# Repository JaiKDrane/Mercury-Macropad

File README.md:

# Mercury

## License

This repository uses a split licensing model:

* **Hardware & CAD ('/hardware', '/cad'):** Licensed under the **CERN Open Hardware Licence Version 2 - Strongly Reciprocal** ([CERN-OHL-S v2](hardware/LICENSE-HARDWARE.txt))
* **Firmware ('/firmware'):** Licensed under the **GNU General Public License v3.0** ([GPLv3](firmware/LICENSE)) due to QMK dependencies.

*Blender rendering of what the finished product might look like.*

## Purpose
The Mercury macropad is a 16+1 key macro pad aimed at being useful for a variety of purposes, featuring an OLED screen, a rotary encoder, and 16 customizable macro-keys. The design is centered around a nice!nano and nice!view, as well as Hotswap Kalih MX sockets.

You can either use the ([.STL](hardware/MercuryCase.stl)) or the ([View-Only Onshape Link](https://cad.onshape.com/documents/36be8d2820c932561b6e754c/w/a382f2a567d932feba75c19c/e/c855985b69218710006a8b27?renderMode=0&uiState=6aff60ae90390abc054af3d9)) to view the design.

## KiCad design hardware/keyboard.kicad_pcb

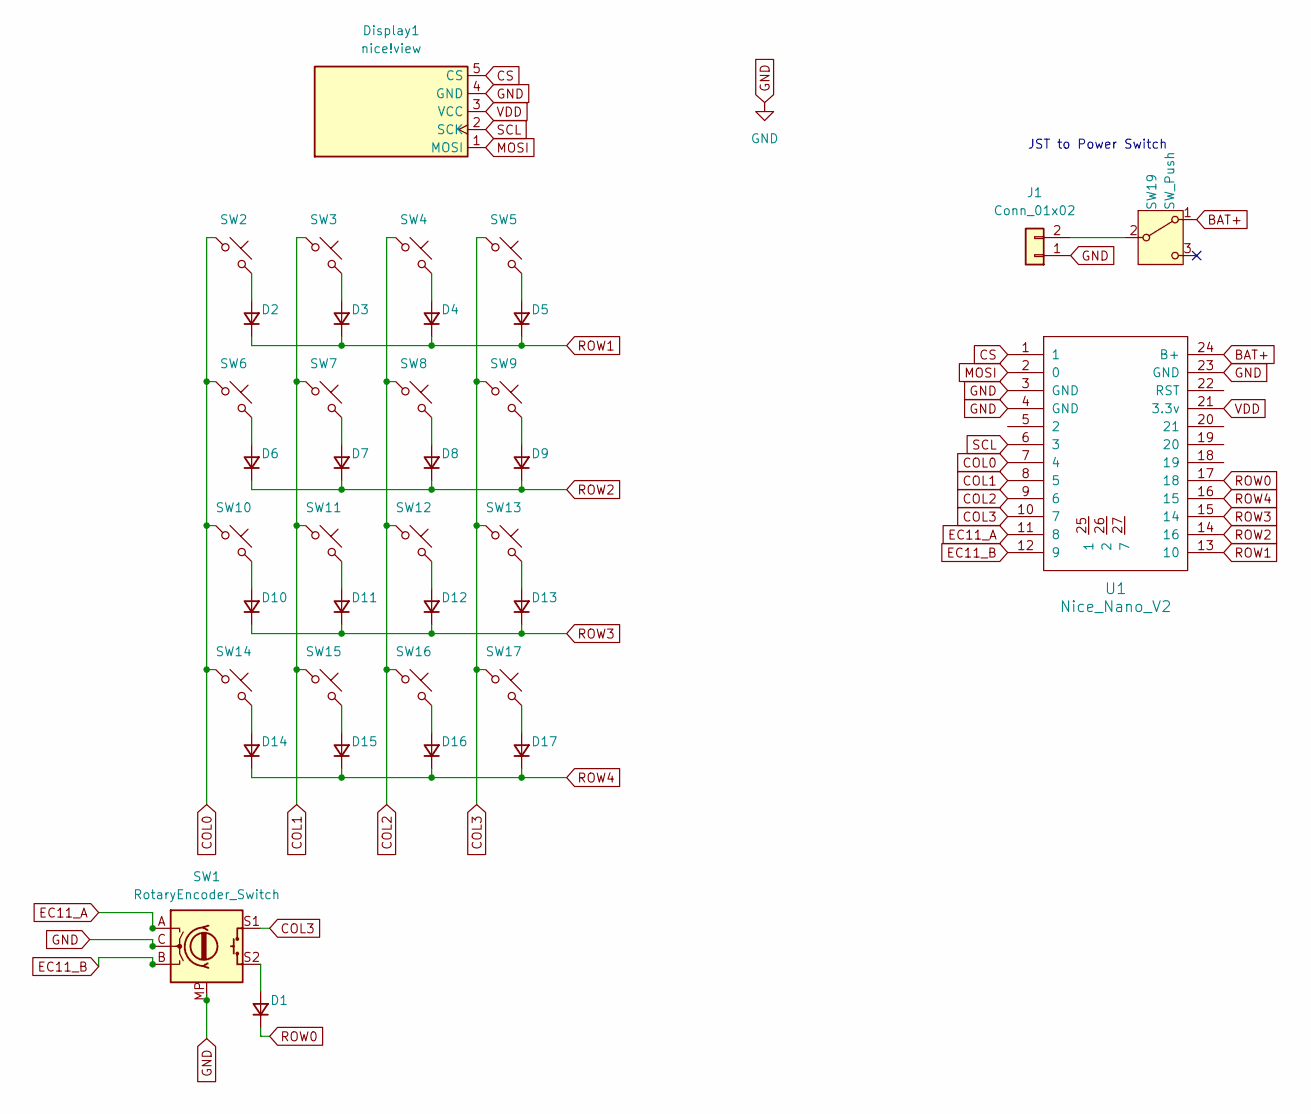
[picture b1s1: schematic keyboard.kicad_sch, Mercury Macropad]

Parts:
D1, D2, D3, D4, D5, D6, D7, D8, D9, D10, D11, D12, D13, D14, D15, D16, D17: D; D_SOD-123
Display1: nice!view; nice_view
J1: Conn_01x02; JST_PH_B2B-PH-K_1x02_P2.00mm_Vertical
SW1: RotaryEncoder_Switch; RotaryEncoder_Alps_EC11E-Switch_Vertical_H20mm
SW2, SW3, SW4, SW5, SW6, SW7, SW8, SW9, SW10, SW11, SW12, SW13, SW14, SW15, SW16, SW17: SW_Push; SW_Hotswap_Kailh_MX_1.00u
SW19: SW_Push; SW_Slide_SPDT_Angled_CK_OS102011MA1Q
U1: Nice_Nano_V2

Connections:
BAT+: SW19.1 (A), U1.24 (B+)
COL0: SW2.1, SW6.1, SW10.1, SW14.1, U1.7 (4)
COL1: SW3.1, SW7.1, SW11.1, SW15.1, U1.8 (5)
COL2: SW4.1, SW8.1, SW12.1, SW16.1, U1.9 (6)
COL3: SW1.S1, SW5.1, SW9.1, SW13.1, SW17.1, U1.10 (7)
CS: Display1.5 (CS), U1.1
EC11_A: SW1.A, U1.11 (8)
EC11_B: SW1.B, U1.12 (9)
GND: Display1.4 (GND), J1.1, SW1.C, SW1.MP, U1.3 (GND), U1.4 (GND), U1.23 (GND)
MOSI: Display1.1 (MOSI), U1.2 (0)
unnamed: D1.2 (A), SW1.S2
unnamed: D2.2 (A), SW2.2
unnamed: D3.2 (A), SW3.2
unnamed: D4.2 (A), SW4.2
unnamed: D5.2 (A), SW5.2
unnamed: D6.2 (A), SW6.2
unnamed: D7.2 (A), SW7.2
unnamed: D8.2 (A), SW8.2
unnamed: D9.2 (A), SW9.2
unnamed: D10.2 (A), SW10.2
unnamed: D11.2 (A), SW11.2
unnamed: D12.2 (A), SW12.2
unnamed: D13.2 (A), SW13.2
unnamed: D14.2 (A), SW14.2
unnamed: D15.2 (A), SW15.2
unnamed: D16.2 (A), SW16.2
unnamed: D17.2 (A), SW17.2
unnamed: J1.2, SW19.2 (B)
ROW0: D1.1 (K), U1.17 (18)
ROW1: D2.1 (K), D3.1 (K), D4.1 (K), D5.1 (K), U1.13 (10)
ROW2: D6.1 (K), D7.1 (K), D8.1 (K), D9.1 (K), U1.14 (16)
ROW3: D10.1 (K), D11.1 (K), D12.1 (K), D13.1 (K), U1.15 (14)
ROW4: D14.1 (K), D15.1 (K), D16.1 (K), D17.1 (K), U1.16 (15)
SCL: Display1.2 (SCK), U1.6 (3)
VDD: Display1.3 (VCC), U1.21 (3.3v)

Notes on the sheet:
JST to Power Switch

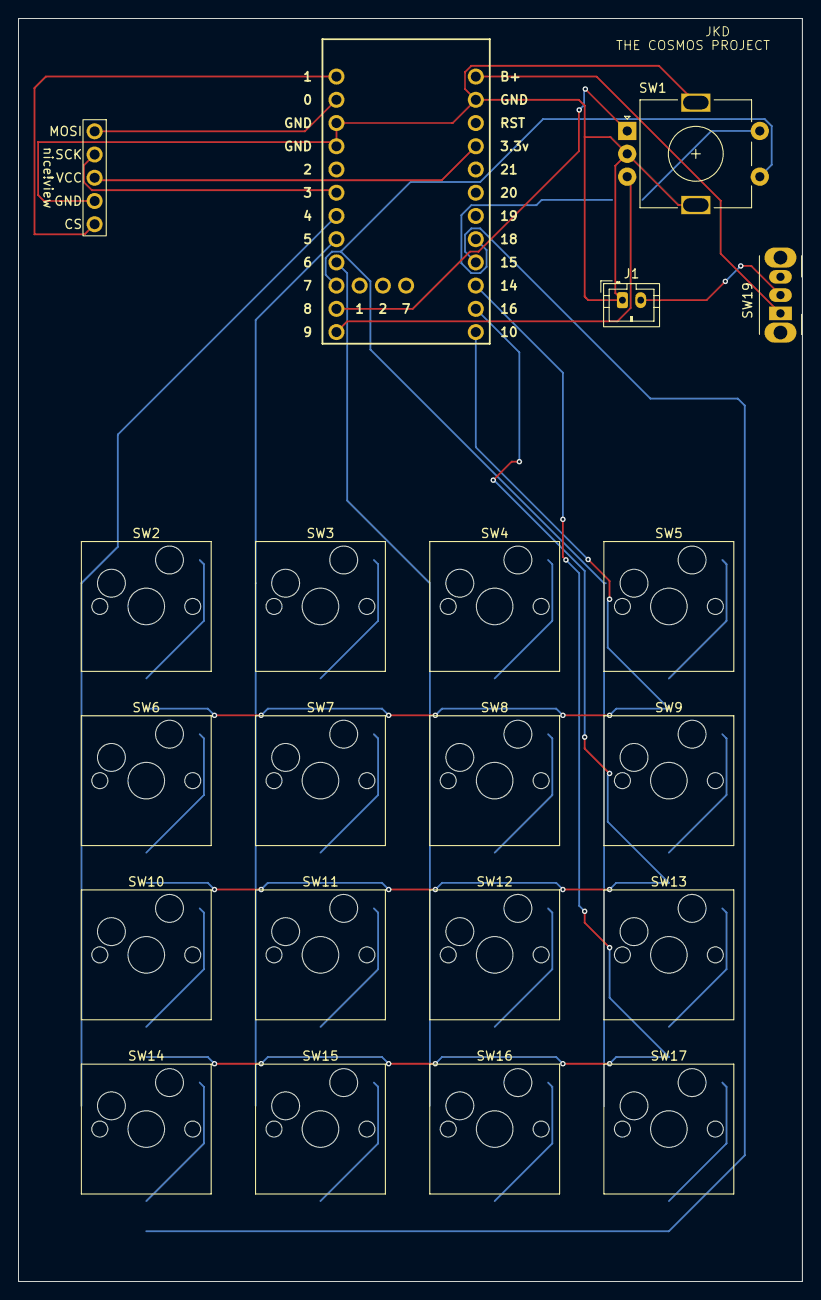
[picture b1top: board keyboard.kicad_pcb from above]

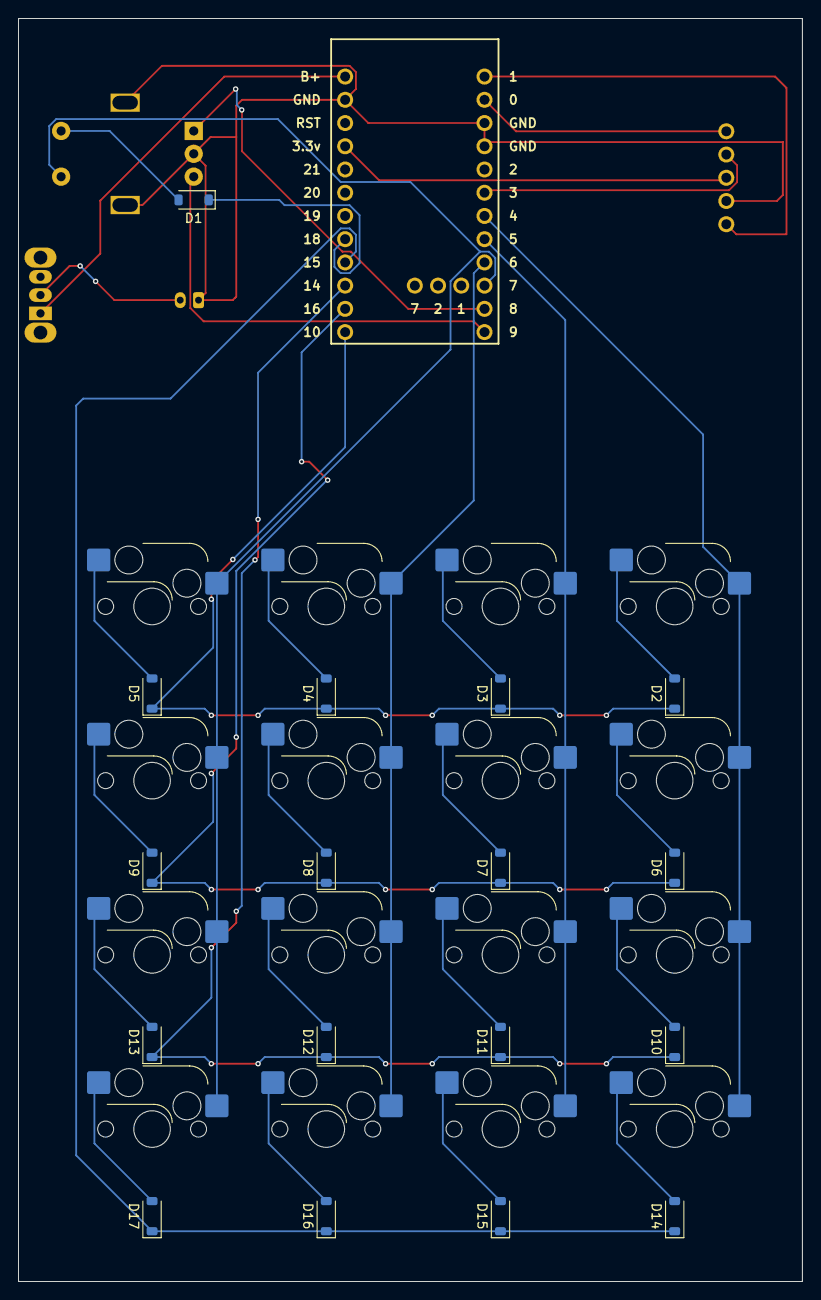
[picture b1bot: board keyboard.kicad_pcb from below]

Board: 2 copper layers, 85.7 x 138.1 mm, 38 parts (17 on the bottom side), 35 nets.

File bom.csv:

Designator,Footprint,Quantity,Value,LCSC Part #
"D1, D10, D11, D12, D13, D14, D15, D16, D17, D2, D3, D4, D5, D6, D7, D8, D9",D_SOD-123,17,D,
DISPLAY1,nice_view,1,nice!view,
J1,JST_PH_B2B-PH-K_1x02_P2.00mm_Vertical,1,Conn_01x02,
SW1,RotaryEncoder_Alps_EC11E-Switch_Vertical_H20mm,1,RotaryEncoder_Switch,
"SW10, SW11, SW12, SW13, SW14, SW15, SW16, SW17, SW2, SW3, SW4, SW5, SW6, SW7, SW8, SW9",SW_Hotswap_Kailh_MX_1.00u,16,SW_Push,
SW19,SW_Slide_SPDT_Angled_CK_OS102011MA1Q,1,SW_Push,
U1,Nice_Nano_V2,1,Nice_Nano_V2,

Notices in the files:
hardware/keyboard.kicad_pcb:
Licensed under CERN-OHL-S v2
